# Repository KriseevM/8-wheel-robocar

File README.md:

# 8-колёсный робот Корсак
## Платы
В данный момент используется единственная плата управления и контроллер Arduino Uno

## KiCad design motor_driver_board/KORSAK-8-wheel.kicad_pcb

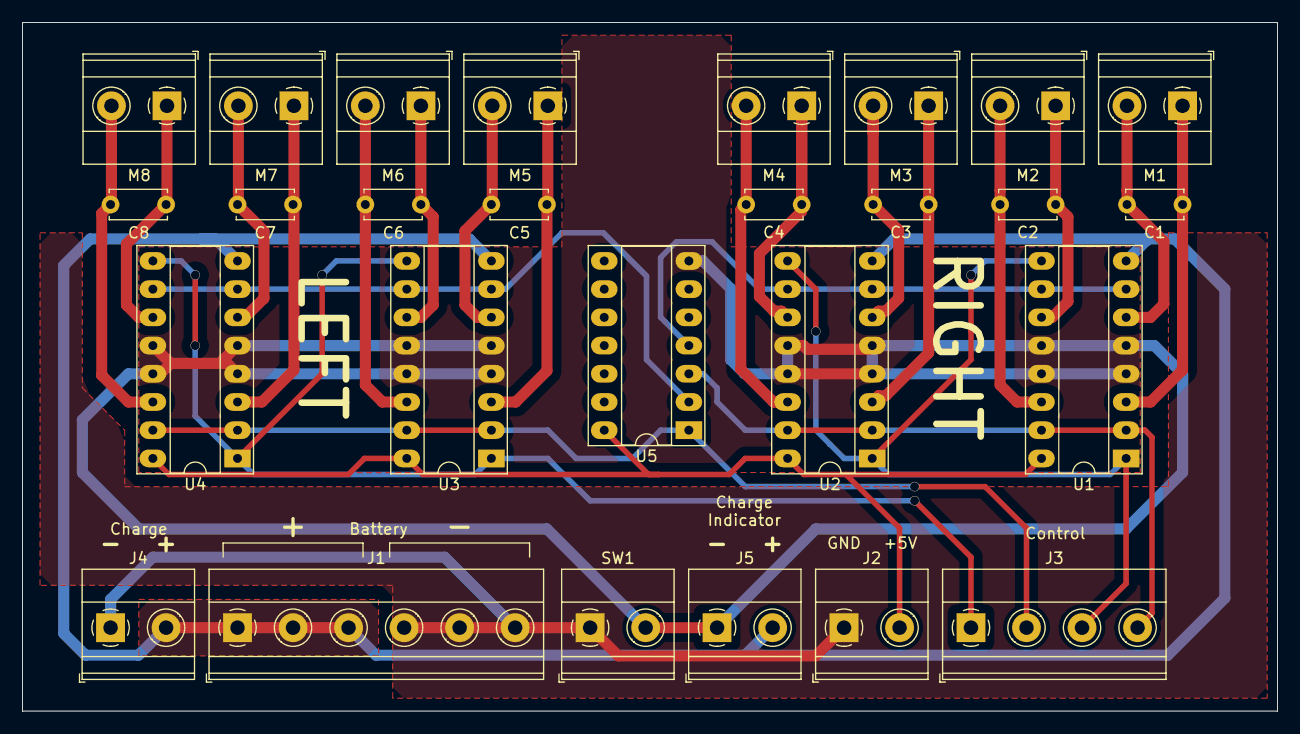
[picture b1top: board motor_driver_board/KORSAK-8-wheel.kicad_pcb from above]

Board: 2 copper layers, 113.0 x 62.0 mm, 27 parts (0 on the bottom side), 26 nets.

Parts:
C1, C2, C3, C4, C5, C6, C7, C8: 10pF; C_Disc_D5.0mm_W2.5mm_P5.00mm
J1: Battery; TerminalBlock_Phoenix_MKDS-1,5-6_1x06_P5.00mm_Horizontal
J2: 5V Power; TerminalBlock_Phoenix_MKDS-1,5-2_1x02_P5.00mm_Horizontal
J3: Logic Connector; TerminalBlock_Phoenix_MKDS-1,5-4_1x04_P5.00mm_Horizontal
J4: Charger; TerminalBlock_Phoenix_MKDS-1,5-2_1x02_P5.00mm_Horizontal
J5: Charge Indicator; TerminalBlock_Phoenix_MKDS-1,5-2_1x02_P5.00mm_Horizontal
M1, M2, M3, M4, M5, M6, M7, M8: Motor_DC; TerminalBlock_Phoenix_MKDS-1,5-2_1x02_P5.00mm_Horizontal
SW1: SW_SPST; TerminalBlock_Phoenix_MKDS-1,5-2_1x02_P5.00mm_Horizontal
U1, U2, U3, U4: L293D; DIP-16_W7.62mm_Socket_LongPads
U5: 74LS04; DIP-14_W7.62mm_Socket_LongPads

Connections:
+5V: J2.2, U1.16, U2.16, U3.16, U4.16, U5.14
+BATT: J1.1, J1.2, J1.3, J4.2, J5.2, U1.8, U2.8, U3.8, U4.8
/-BATT: J1.4, J1.5, J1.6, J2.1, J4.1, SW1.1
/L_EN: J3.1, U3.1, U3.9, U4.1, U4.9
/L_IN_1: J3.2, U3.2, U3.15, U4.2, U4.15, U5.1
/L_IN_2: U3.7, U3.10, U4.7, U4.10, U5.2
/M1_OUT_1: C1.1, M1.1, U1.3
/M1_OUT_2: C1.2, M1.2, U1.6
/M2_OUT_1: C2.1, M2.1, U1.11
/M2_OUT_2: C2.2, M2.2, U1.14
/M3_OUT_1: C3.1, M3.1, U2.3
/M3_OUT_2: C3.2, M3.2, U2.6
/M4_OUT_1: C4.1, M4.1, U2.11
/M4_OUT_2: C4.2, M4.2, U2.14
/M5_OUT_1: C6.2, M6.1, U3.11
/M5_OUT_2: C6.1, M6.2, U3.14
/M6_OUT_1: C5.2, M5.1, U3.3
/M6_OUT_2: C5.1, M5.2, U3.6
/M7_OUT_1: C8.2, M8.1, U4.11
/M7_OUT_2: C8.1, M8.2, U4.14
/M8_OUT_1: C7.2, M7.1, U4.3
/M8_OUT_2: C7.1, M7.2, U4.6
/R_EN: J3.3, U1.1, U1.9, U2.1, U2.9
/R_IN_1: J3.4, U1.2, U1.15, U2.2, U2.15, U5.3
/R_IN_2: U1.7, U1.10, U2.7, U2.10, U5.4
GND: J5.1, SW1.2, U1.4, U1.5, U1.12, U1.13, U2.4, U2.5, U2.12, U2.13, U3.4, U3.5, U3.12, U3.13, U4.4, U4.5, U4.12, U4.13, U5.7

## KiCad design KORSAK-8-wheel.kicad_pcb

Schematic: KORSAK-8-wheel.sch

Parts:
J1, J4: Screw_Terminal_01x04; TerminalBlock_Phoenix_MKDS-1,5-4_1x04_P5.00mm_Horizontal
J2: Conn_01x02_Male; PinHeader_1x02_P2.54mm_Horizontal
J3: Screw_Terminal_01x06; TerminalBlock_Phoenix_MKDS-1,5-6_1x06_P5.00mm_Horizontal
M1, M2, M3, M4, M5, M6, M7, M8: Motor_DC; TerminalBlock_Phoenix_MKDS-1,5-2_1x02_P5.00mm_Horizontal
U1, U2, U3, U4: L293D; DIP-16_W7.62mm_Socket

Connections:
+5V: J2.2, U1.16 (VCC1), U2.16 (VCC1), U3.16 (VCC1), U4.16 (VCC1)
GND: J1.2, J1.4, J2.1, J4.2, J4.4, U1.4 (GND), U1.5 (GND), U1.12 (GND), U1.13 (GND), U2.4 (GND), U2.5 (GND), U2.12 (GND), U2.13 (GND), U3.4 (GND), U3.5 (GND), U3.12 (GND), U3.13 (GND), U4.4 (GND), U4.5 (GND), U4.12 (GND), U4.13 (GND)
unnamed: J1.1, U3.8 (VCC2)
unnamed: J1.3, U4.8 (VCC2)
unnamed: J3.1, U2.7 (2A), U2.10 (3A), U4.7 (2A), U4.10 (3A)
unnamed: J3.2, U2.2 (1A), U2.15 (4A), U4.2 (1A), U4.15 (4A)
unnamed: J3.3, U2.1 (EN1,2), U2.9 (EN3,4), U4.1 (EN1,2), U4.9 (EN3,4)
unnamed: J3.4, U1.1 (EN1,2), U1.9 (EN3,4), U3.1 (EN1,2), U3.9 (EN3,4)
unnamed: J3.5, U1.2 (1A), U1.15 (4A), U3.2 (1A), U3.15 (4A)
unnamed: J3.6, U1.7 (2A), U1.10 (3A), U3.7 (2A), U3.10 (3A)
unnamed: J4.1, U1.8 (VCC2)
unnamed: J4.3, U2.8 (VCC2)
unnamed: M1.1 (+), U1.3 (1Y)
unnamed: M1.2 (-), U1.6 (2Y)
unnamed: M2.1 (+), U4.3 (1Y)
unnamed: M2.2 (-), U4.6 (2Y)
unnamed: M3.1 (+), U1.11 (3Y)
unnamed: M3.2 (-), U1.14 (4Y)
unnamed: M4.1 (+), U4.11 (3Y)
unnamed: M4.2 (-), U4.14 (4Y)
unnamed: M5.1 (+), U3.11 (3Y)
unnamed: M5.2 (-), U3.14 (4Y)
unnamed: M6.1 (+), U2.11 (3Y)
unnamed: M6.2 (-), U2.14 (4Y)
unnamed: M7.1 (+), U3.3 (1Y)
unnamed: M7.2 (-), U3.6 (2Y)
unnamed: M8.1 (+), U2.3 (1Y)
unnamed: M8.2 (-), U2.6 (2Y)

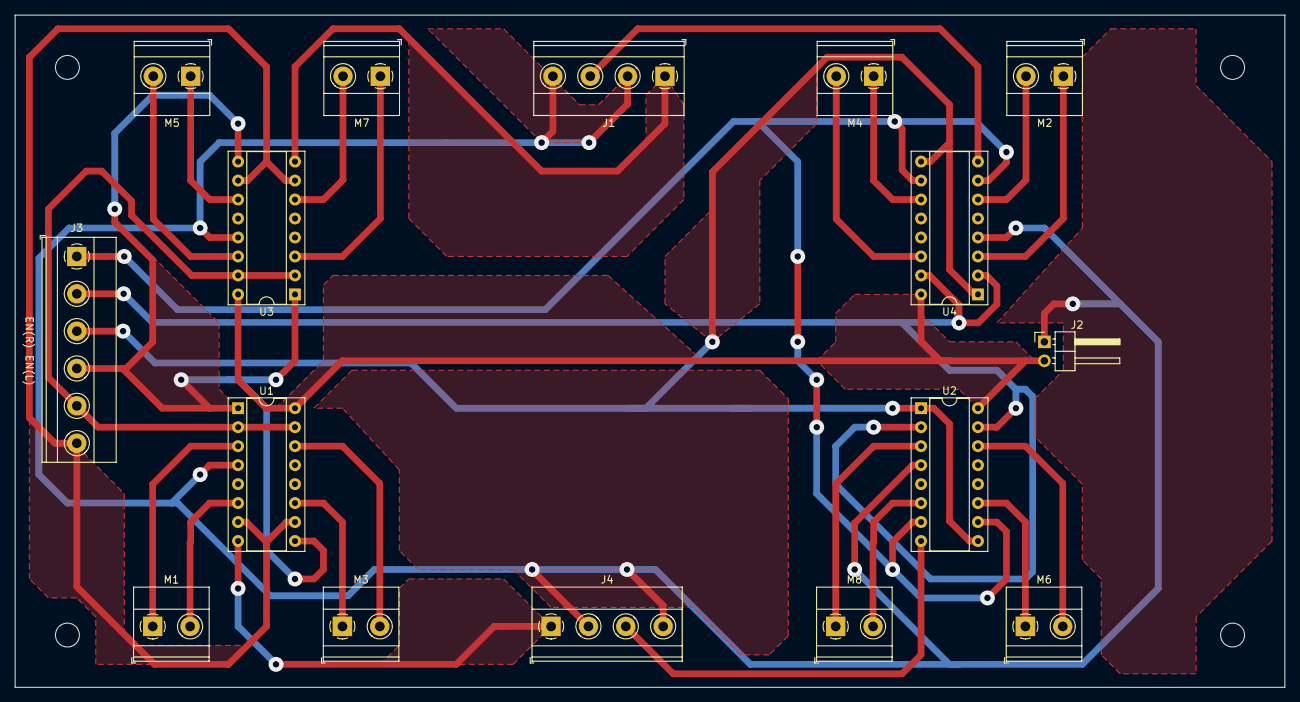
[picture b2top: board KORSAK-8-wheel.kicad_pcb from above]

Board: 2 copper layers, 170.0 x 90.0 mm, 20 parts (0 on the bottom side), 28 nets.

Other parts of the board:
 : MountingHole_3.2mm_M3
 #2,  #3,  #4: MountingHole_3.2mm_M3

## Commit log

2021-02-25 Initial commit Базовый коммит с kicad-файлами основной платы
2021-02-25 Исправил обозначения двигателей в схеме
2021-03-08 Добавил подписи страниц
2021-03-08 Переместил файлы платы в отдельную папку
2021-03-08 Изменил схему питания
2021-03-08 Переместил файлы
2021-03-13 Добавил конденсаторы параллельно двигателям
2021-03-13 Добавил конденсаторы в схему и исправил её
2021-03-13 Откат прошлого коммита, т.к. это незаконченная версия
2021-03-14 Синхронизировал историю коммитов с master веткой
2021-03-14 Добавил выводы под выключатель и индикатор заряда
2021-03-14 Сделал управление через логическое НЕ и метки
2021-03-14 Добавил вывод под зарядник
2021-03-15 Закончил моделировать плату
2021-03-15 Добавил output в gitignore
2021-03-15 Незначительные фиксы
2021-03-15 Исправил полигон рядом с BATT-
